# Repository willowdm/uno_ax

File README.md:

# uno_ax
kiCad ax5043 arduino Shield

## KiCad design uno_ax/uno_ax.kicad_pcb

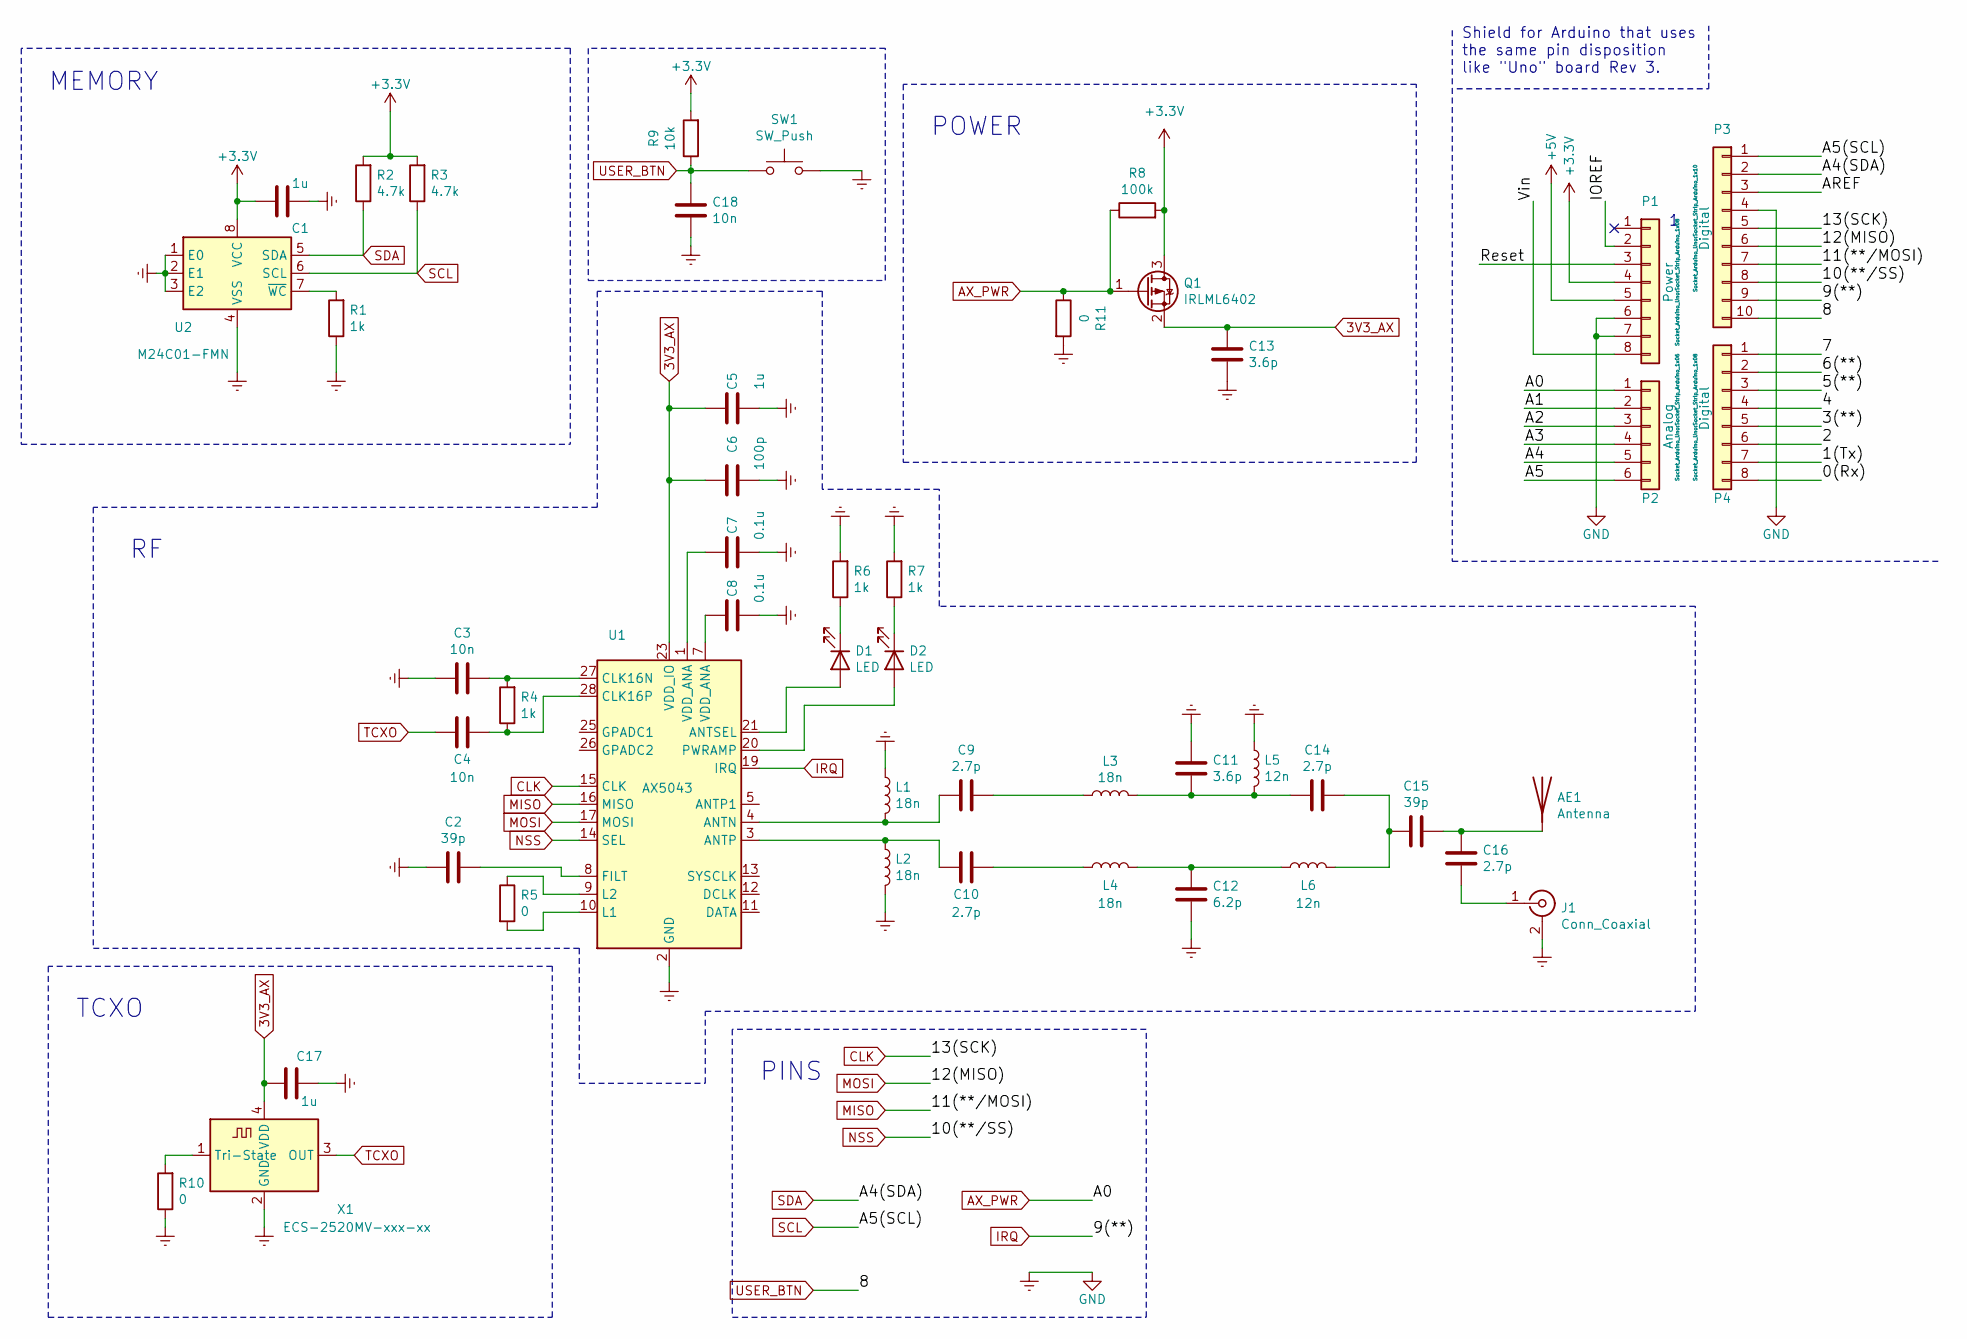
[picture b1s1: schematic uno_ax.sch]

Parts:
AE1: Antenna; Texas_SWRA416_868MHz_915MHz
C1, C5, C17: 1u; C_0603_1608Metric
C2, C15: 39p; C_0603_1608Metric
C3, C4, C18: 10n; C_0603_1608Metric
C6: 100p; C_0603_1608Metric
C7, C8: 0.1u; C_0603_1608Metric
C9, C10, C14, C16: 2.7p; C_0603_1608Metric
C11, C13: 3.6p; C_0603_1608Metric
C12: 6.2p; C_0603_1608Metric
D1, D2: LED; LED_0603_1608Metric
J1: Conn_Coaxial; SMB_Jack_Vertical
L1, L2, L3, L4: 18n; L_0603_1608Metric
L5, L6: 12n; L_0603_1608Metric
P1: Power; Socket_Strip_Arduino_1x08
P2: Analog; Socket_Strip_Arduino_1x06
P3: Digital; Socket_Strip_Arduino_1x10
P4: Digital; Socket_Strip_Arduino_1x08
Q1: IRLML6402; SOT-23
R1, R4, R6, R7: 1k; R_0603_1608Metric
R2, R3: 4.7k; R_0603_1608Metric
R5, R10, R11: 0; R_0603_1608Metric
R8: 100k; R_0603_1608Metric
R9: 10k; R_0603_1608Metric
SW1: SW_Push; SW_Push_1P1T_NO_CK_KSC6xxJ
U1: AX5043; QFN-28-1EP_5x5mm_P0.5mm_EP3.35x3.35mm
U2: M24C01-FMN; SOIC-8_3.9x4.9mm_P1.27mm
X1: ECS-2520MV-xxx-xx; Oscillator_SMD_ECS_2520MV-xxx-xx-4Pin_2.5x2.0mm

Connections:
3V3_AX: C5.1, C6.1, C13.2, C17.1, Q1.2 (S), U1.23 (VDD_IO), X1.4 (VDD)
+3V3: C1.2, P1.4, Q1.3 (D), R2.2, R3.2, R8.2, R9.2, U2.8 (VCC)
+5V: P1.5
/0(Rx): P4.8
/1(Tx): P4.7
/2: P4.6
/3(**): P4.5
/4: P4.4
/5(**): P4.3
/6(**): P4.2
/7: P4.1
/A1: P2.2
/A2: P2.3
/A3: P2.4
/A4: P2.5
/A5: P2.6
/AREF: P3.3
/IOREF: P1.2
/Reset: P1.3
/Vin: P1.8
AX_PWR: P2.1, Q1.1 (G), R8.1, R11.1
CLK: P3.5, U1.15 (CLK)
Earth: C1.1, C2.2, C3.2, C5.2, C6.2, C7.2, C8.2, C11.2, C12.1, C13.1, C17.2, C18.1, J1.2 (Ext), L1.1, L2.2, L5.1, P1.6, P1.7, P3.4, R1.1, R6.2, R7.2, R10.1, R11.2, SW1.2, U1.2 (GND), U1.6 (GND), U1.29 (GND), U2.1 (E0), U2.2 (E1), U2.3 (E2), U2.4 (VSS), X1.2 (GND)
IRQ: P3.9, U1.19 (IRQ)
MISO: P3.7, U1.16 (MISO)
MOSI: P3.6, U1.17 (MOSI)
NSS: P3.8, U1.14 (SEL)
unnamed: AE1.1, C15.1, C16.2
unnamed: C2.1, U1.8 (FILT)
unnamed: C3.1, R4.2, U1.27 (CLK16N)
unnamed: C4.2, R4.1, U1.28 (CLK16P)
unnamed: C7.1, U1.1 (VDD_ANA)
unnamed: C8.1, U1.7 (VDD_ANA)
unnamed: C9.1, L3.1
unnamed: C9.2, L1.2, U1.4 (ANTN)
unnamed: C10.1, L4.1
unnamed: C10.2, L2.1, U1.3 (ANTP)
unnamed: C11.1, C14.2, L3.2, L5.2
unnamed: C12.2, L4.2, L6.1
unnamed: C14.1, C15.2, L6.2
unnamed: C16.1, J1.1 (In)
unnamed: D1.1 (K), R6.1
unnamed: D1.2 (A), U1.21 (ANTSEL)
unnamed: D2.1 (K), R7.1
unnamed: D2.2 (A), U1.20 (PWRAMP)
unnamed: R1.2, U2.7 (~WC)
unnamed: R5.1, U1.9 (L2)
unnamed: R5.2, U1.10 (L1)
unnamed: R10.2, X1.1 (Tri-State)
SCL: P3.1, R3.1, U2.6 (SCL)
SDA: P3.2, R2.1, U2.5 (SDA)
TCXO: C4.1, X1.3 (OUT)
USER_BTN: C18.2, P3.10, R9.1, SW1.1

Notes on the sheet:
TCXO
PINS
POWER
MEMORY
Shield for Arduino that uses the same pin disposition like "Uno" board Rev 3.

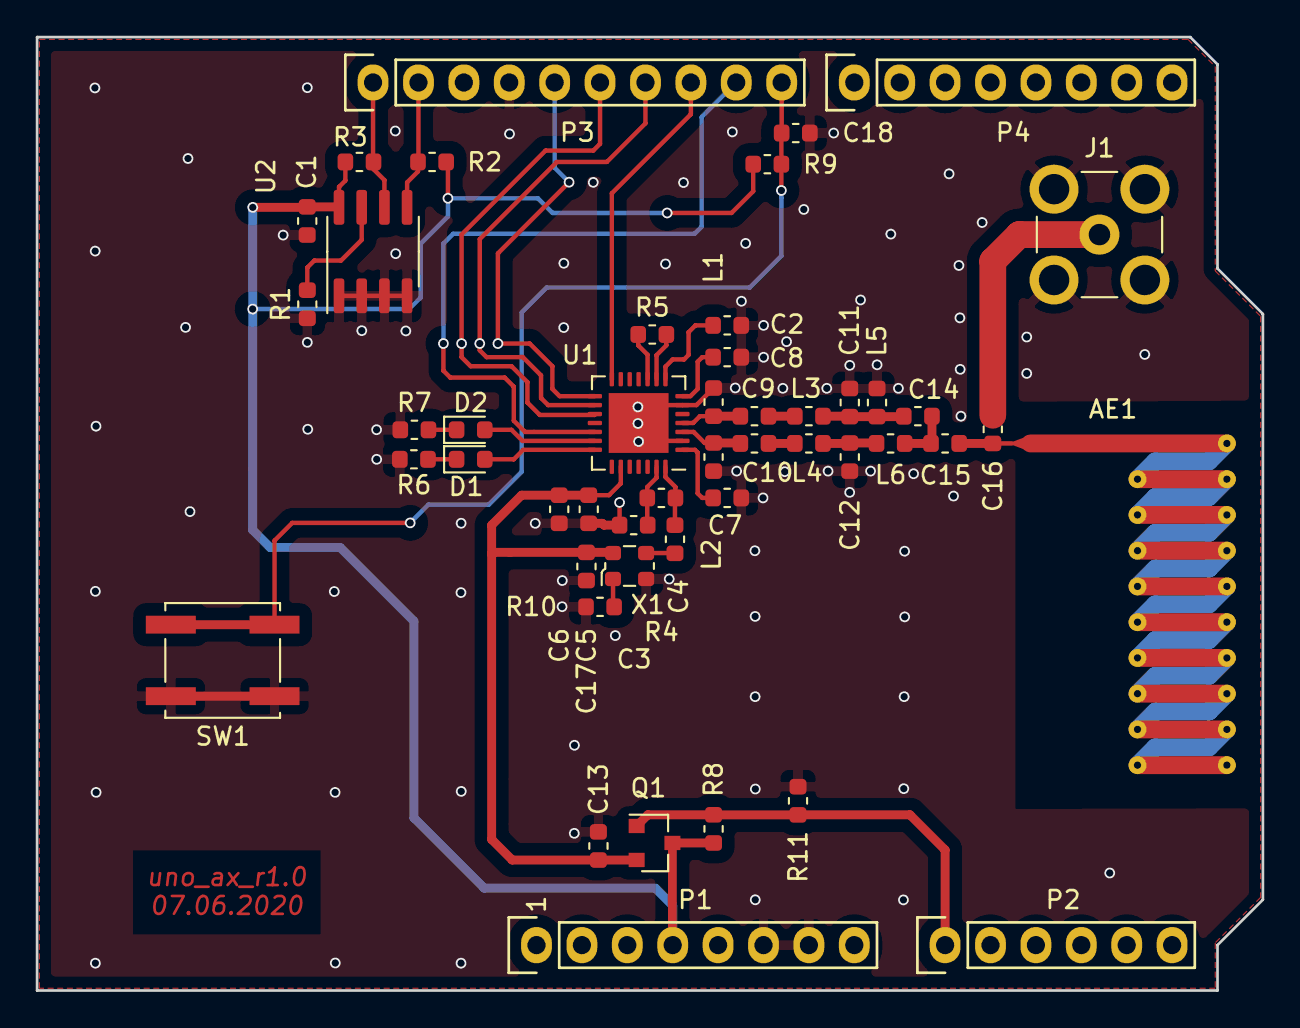
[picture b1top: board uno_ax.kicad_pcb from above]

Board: 2 copper layers, 68.6 x 53.3 mm, 48 parts (0 on the bottom side), 35 nets.

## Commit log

2020-08-05 inint uno_ax r1.0
